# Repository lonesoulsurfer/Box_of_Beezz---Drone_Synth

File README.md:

# Box of Beezz: drone synth

Box of Beezz is a drone synth with 9 transistor oscillators. Each oscillator has an LED that flashes with its signal.

## Build guide and video

- Step-by-step build guide on Instructables: [Box of Beezz Drone Synth](https://www.instructables.com/Box-of-Beezz-Drone-Synth/)
- Video on YouTube: [Box of Beezz](https://www.youtube.com/watch?v=Lz0C1BahfkU)

## How it works

- Each oscillator is a relaxation oscillator. A capacitor charges to a threshold, then a transistor discharges it. This repeats, and makes a sawtooth wave.
- Different capacitor values give different frequencies.
- 9 oscillators together make a rich drone sound.
- A master tone knob changes the sound.
- A control voltage (CV) output lets you connect the synth to a sequencer.

## What you need

- All parts are in the parts list (`Drone Synth - Parts List.xlsx`).
- There are two versions of the PCB:
  - Version 1: the Gerber files are in `Drone Synth V1 - gerber files.zip`. The Eagle files and the schematic are in `Box of Beezz - Drone Synth V1/`.
  - Version 2: the Gerber files, the Eagle files and the schematic are in `Box of Beezz - Drone Synth V2/`.
- There are two front panel designs, with and without a speaker. They are in `Front Panel/`.

## Build it

The Instructables guide shows each step, with photos. In short:

1. Send the Gerber files to a PCB maker.
2. Get the parts in the parts list.
3. Solder the parts to the PCB.
4. Connect the power and test the circuit.

## Files in this repository

| Folder or file | Contents |
|----------------|----------|
| `Drone Synth V1 - gerber files.zip` | Gerber files for the version 1 PCB, ready to order |
| `Box of Beezz - Drone Synth V1/` | Eagle files and schematic for version 1 |
| `Box of Beezz - Drone Synth V2/` | Gerber files, Eagle files and schematic for version 2 |
| `Front Panel/` | Front panel designs, with and without a speaker (SVG and PDF) |
| `Drone Synth - Parts List.xlsx` | Parts list |

## Credits

- Based on the simple oscillator in the [Circle Drone of Doom](https://www.lookmumnocomputer.com/projects#/circledroneofdoom) by Look Mum No Computer.
- PCB and build: Marcus ([lonesoulsurfer](https://github.com/lonesoulsurfer)).

## Support

Do you like this project? You can support my work on [GitHub Sponsors](https://github.com/sponsors/lonesoulsurfer).

## Licence

This project uses the [CERN Open Hardware Licence v2, Strongly Reciprocal](LICENSE) (CERN-OHL-S-2.0). Copyright (c) 2025 Marcus (lonesoulsurfer).

You can make, change and sell boards from these files. If you share or sell a changed design, you must also share the changed design files under the same licence.

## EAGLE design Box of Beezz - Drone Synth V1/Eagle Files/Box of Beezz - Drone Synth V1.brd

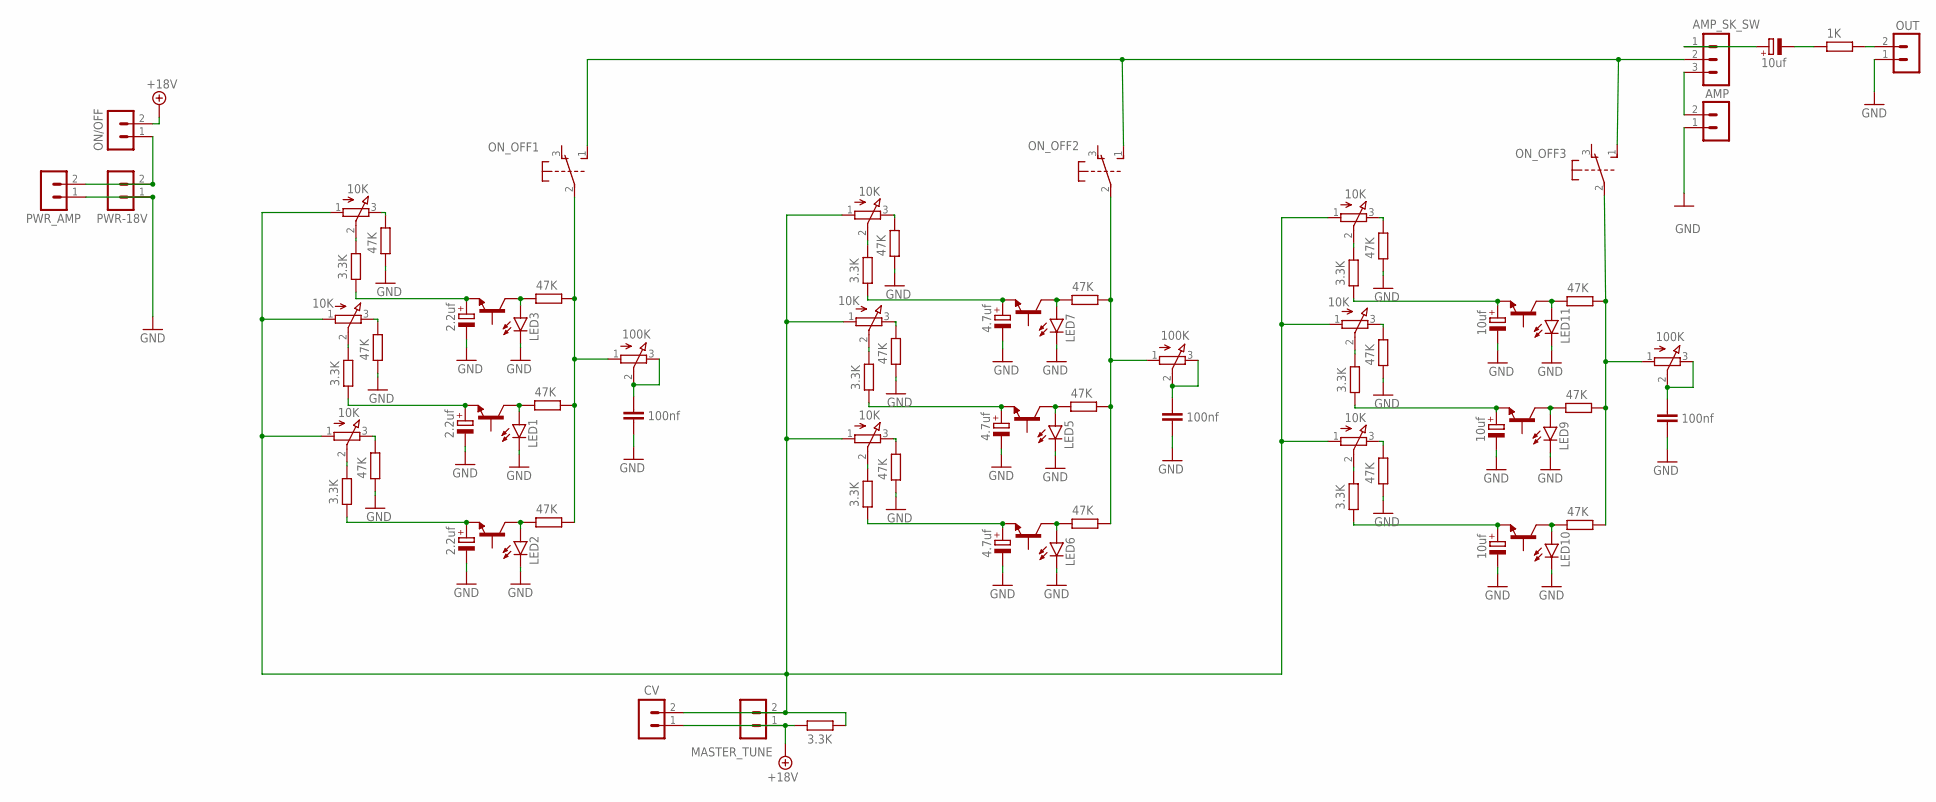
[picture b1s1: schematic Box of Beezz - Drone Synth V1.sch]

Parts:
AMP: B2B-PH-KL; B2B-PH-K-S
AMP_SK_SW: B3B-PH-K-S
C1, C2, C3: 2.2uf; E2-5
C4, C11, C12, C13: 10uf; E2-5
C5, C7, C8: 4.7uf; E2-5
C6, C10, C15: 100nf; C050-024X044
CV: B2B-PH-KL; B2B-PH-K-S
LED1, LED2, LED3, LED5, LED6, LED7, LED9, LED10, LED11: LED3MM
MASTER_TUNE: B2B-PH-KL; B2B-PH-K-S
ON/OFF: B2B-PH-KL; B2B-PH-K-S
ON_OFF1, ON_OFF2, ON_OFF3: SWITCH-6PIN
OUT: B2B-PH-KL; B2B-PH-K-S
PWR-18V: B2B-PH-KL; B2B-PH-K-S
PWR_AMP: B2B-PH-KL; B2B-PH-K-S
R1, R5, R8, R13, R14, R17, R18, R20, R21, R27, R31, R34, R36, R37, R38, R39, R40, R41: 47K; 0207/10
R2, R6, R9, R15, R19, R22, R28, R32, R35: 10K; EVUF
R3, R16, R29: 100K; EVUF
R4, R7, R10, R11, R23, R24, R25, R26, R30, R33: 3.3K; 0207/10
R12: 1K; 0207/10
T1, T2, T3, T5, T6, T7, T9, T10, T11: 2N3904; TO92

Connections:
+12V: CV.1, MASTER_TUNE.1, ON/OFF.2, R11.1
GND: AMP.1, C1.-, C2.-, C3.-, C5.-, C6.2, C7.-, C8.-, C10.2, C11.-, C12.-, C13.-, C15.2, LED1.K (C), LED2.K (C), LED3.K (C), LED5.K (C), LED6.K (C), LED7.K (C), LED9.K (C), LED10.K (C), LED11.K (C), OUT.1, PWR-18V.1, PWR_AMP.1, R13.1, R17.1, R20.1, R36.1, R37.1, R38.1, R39.1, R40.1, R41.1
unnamed: C1.+, R7.1, T1.3 (E)
unnamed: R4.2, R9.2 (S)
unnamed: CV.2, MASTER_TUNE.2, R2.1 (A), R6.1 (A), R9.1 (A), R11.2, R15.1 (A), R19.1 (A), R22.1 (A), R28.1 (A), R32.1 (A), R35.1 (A)
unnamed: LED1.A, R1.1, T1.1 (C)
unnamed: LED2.A, R5.1, T2.1 (C)
unnamed: C2.+, R10.1, T2.3 (E)
unnamed: R2.2 (S), R7.2
unnamed: LED3.A, R8.1, T3.1 (C)
unnamed: C3.+, R4.1, T3.3 (E)
unnamed: R6.2 (S), R10.2
unnamed: R6.3 (E), R20.2
unnamed: R2.3 (E), R17.2
unnamed: R9.3 (E), R13.2
unnamed: LED5.A, R14.1, T5.1 (C)
unnamed: C8.+, R23.1, T7.3 (E)
unnamed: ON/OFF.1, PWR-18V.2, PWR_AMP.2
unnamed: C6.1, R3.2 (S), R3.3 (E)
unnamed: R28.2 (S), R30.2
unnamed: LED6.A, R18.1, T6.1 (C)
unnamed: C5.+, R24.1, T5.3 (E)
unnamed: R32.2 (S), R33.2
unnamed: ON_OFF1.2, R1.2, R3.1 (A), R5.2, R8.2
unnamed: C7.+, R25.1, T6.3 (E)
unnamed: ON_OFF2.2, R14.2, R16.1 (A), R18.2, R21.2
unnamed: ON_OFF3.2, R27.2, R29.1 (A), R31.2, R34.2
unnamed: C4.-, R12.1
unnamed: AMP_SK_SW.1, C4.+
unnamed: C10.1, R16.2 (S), R16.3 (E)
unnamed: OUT.2, R12.2
unnamed: LED9.A, R27.1, T9.1 (C)
unnamed: C13.+, R26.1, T11.3 (E)
unnamed: AMP.2, AMP_SK_SW.3
unnamed: LED10.A, R31.1, T10.1 (C)
unnamed: C11.+, R30.1, T9.3 (E)
unnamed: R26.2, R35.2 (S)
unnamed: LED11.A, R34.1, T11.1 (C)
unnamed: C12.+, R33.1, T10.3 (E)
unnamed: R22.2 (S), R23.2
unnamed: R15.2 (S), R24.2
unnamed: R19.2 (S), R25.2
unnamed: LED7.A, R21.1, T7.1 (C)
unnamed: C15.1, R29.2 (S), R29.3 (E)
unnamed: AMP_SK_SW.2, ON_OFF1.1 (S), ON_OFF2.1 (S), ON_OFF3.1 (S)
unnamed: R32.3 (E), R41.2
unnamed: R28.3 (E), R40.2
unnamed: R35.3 (E), R39.2
unnamed: R22.3 (E), R36.2
unnamed: R15.3 (E), R37.2
unnamed: R19.3 (E), R38.2

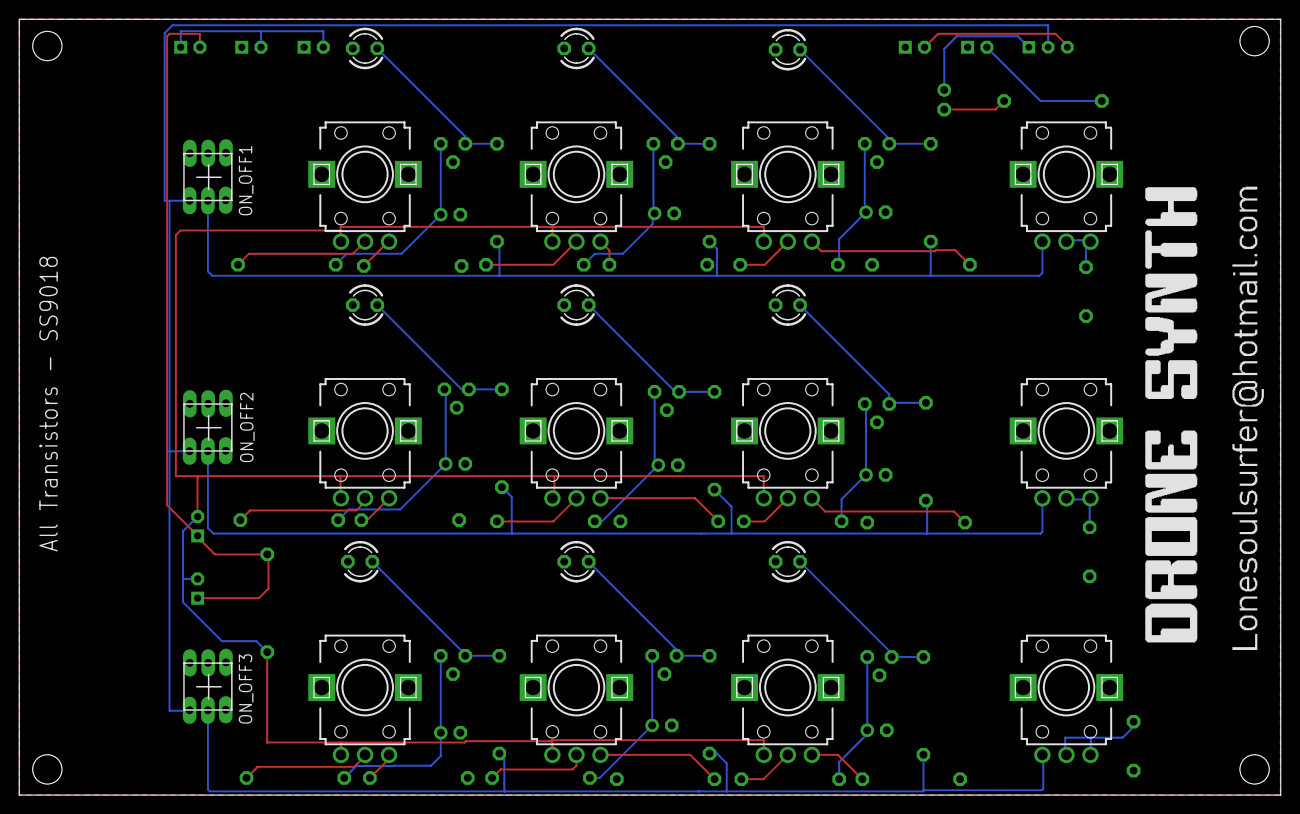
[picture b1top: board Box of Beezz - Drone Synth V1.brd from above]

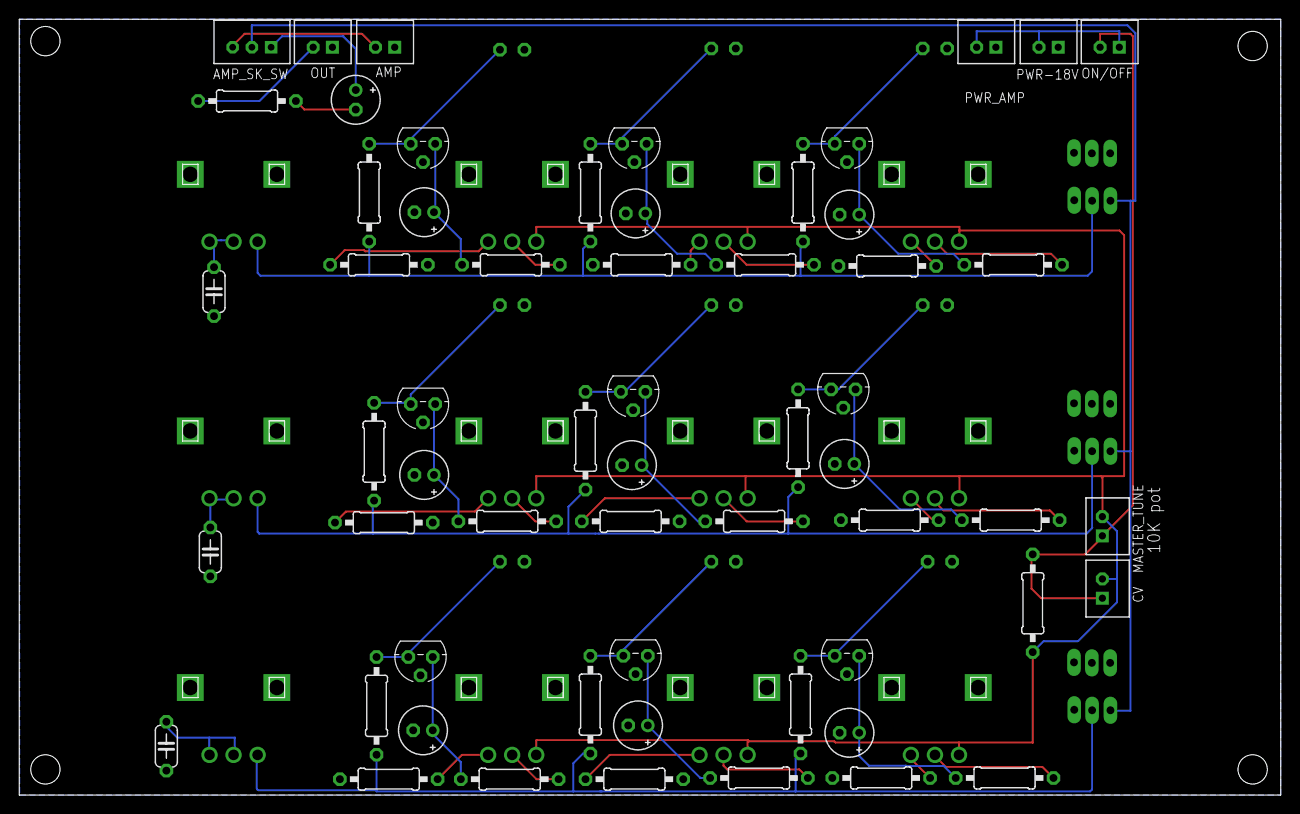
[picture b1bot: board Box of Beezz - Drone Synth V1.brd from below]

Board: 2 copper layers, 131.1 x 80.6 mm, 83 parts (59 on the bottom side), 51 nets.
